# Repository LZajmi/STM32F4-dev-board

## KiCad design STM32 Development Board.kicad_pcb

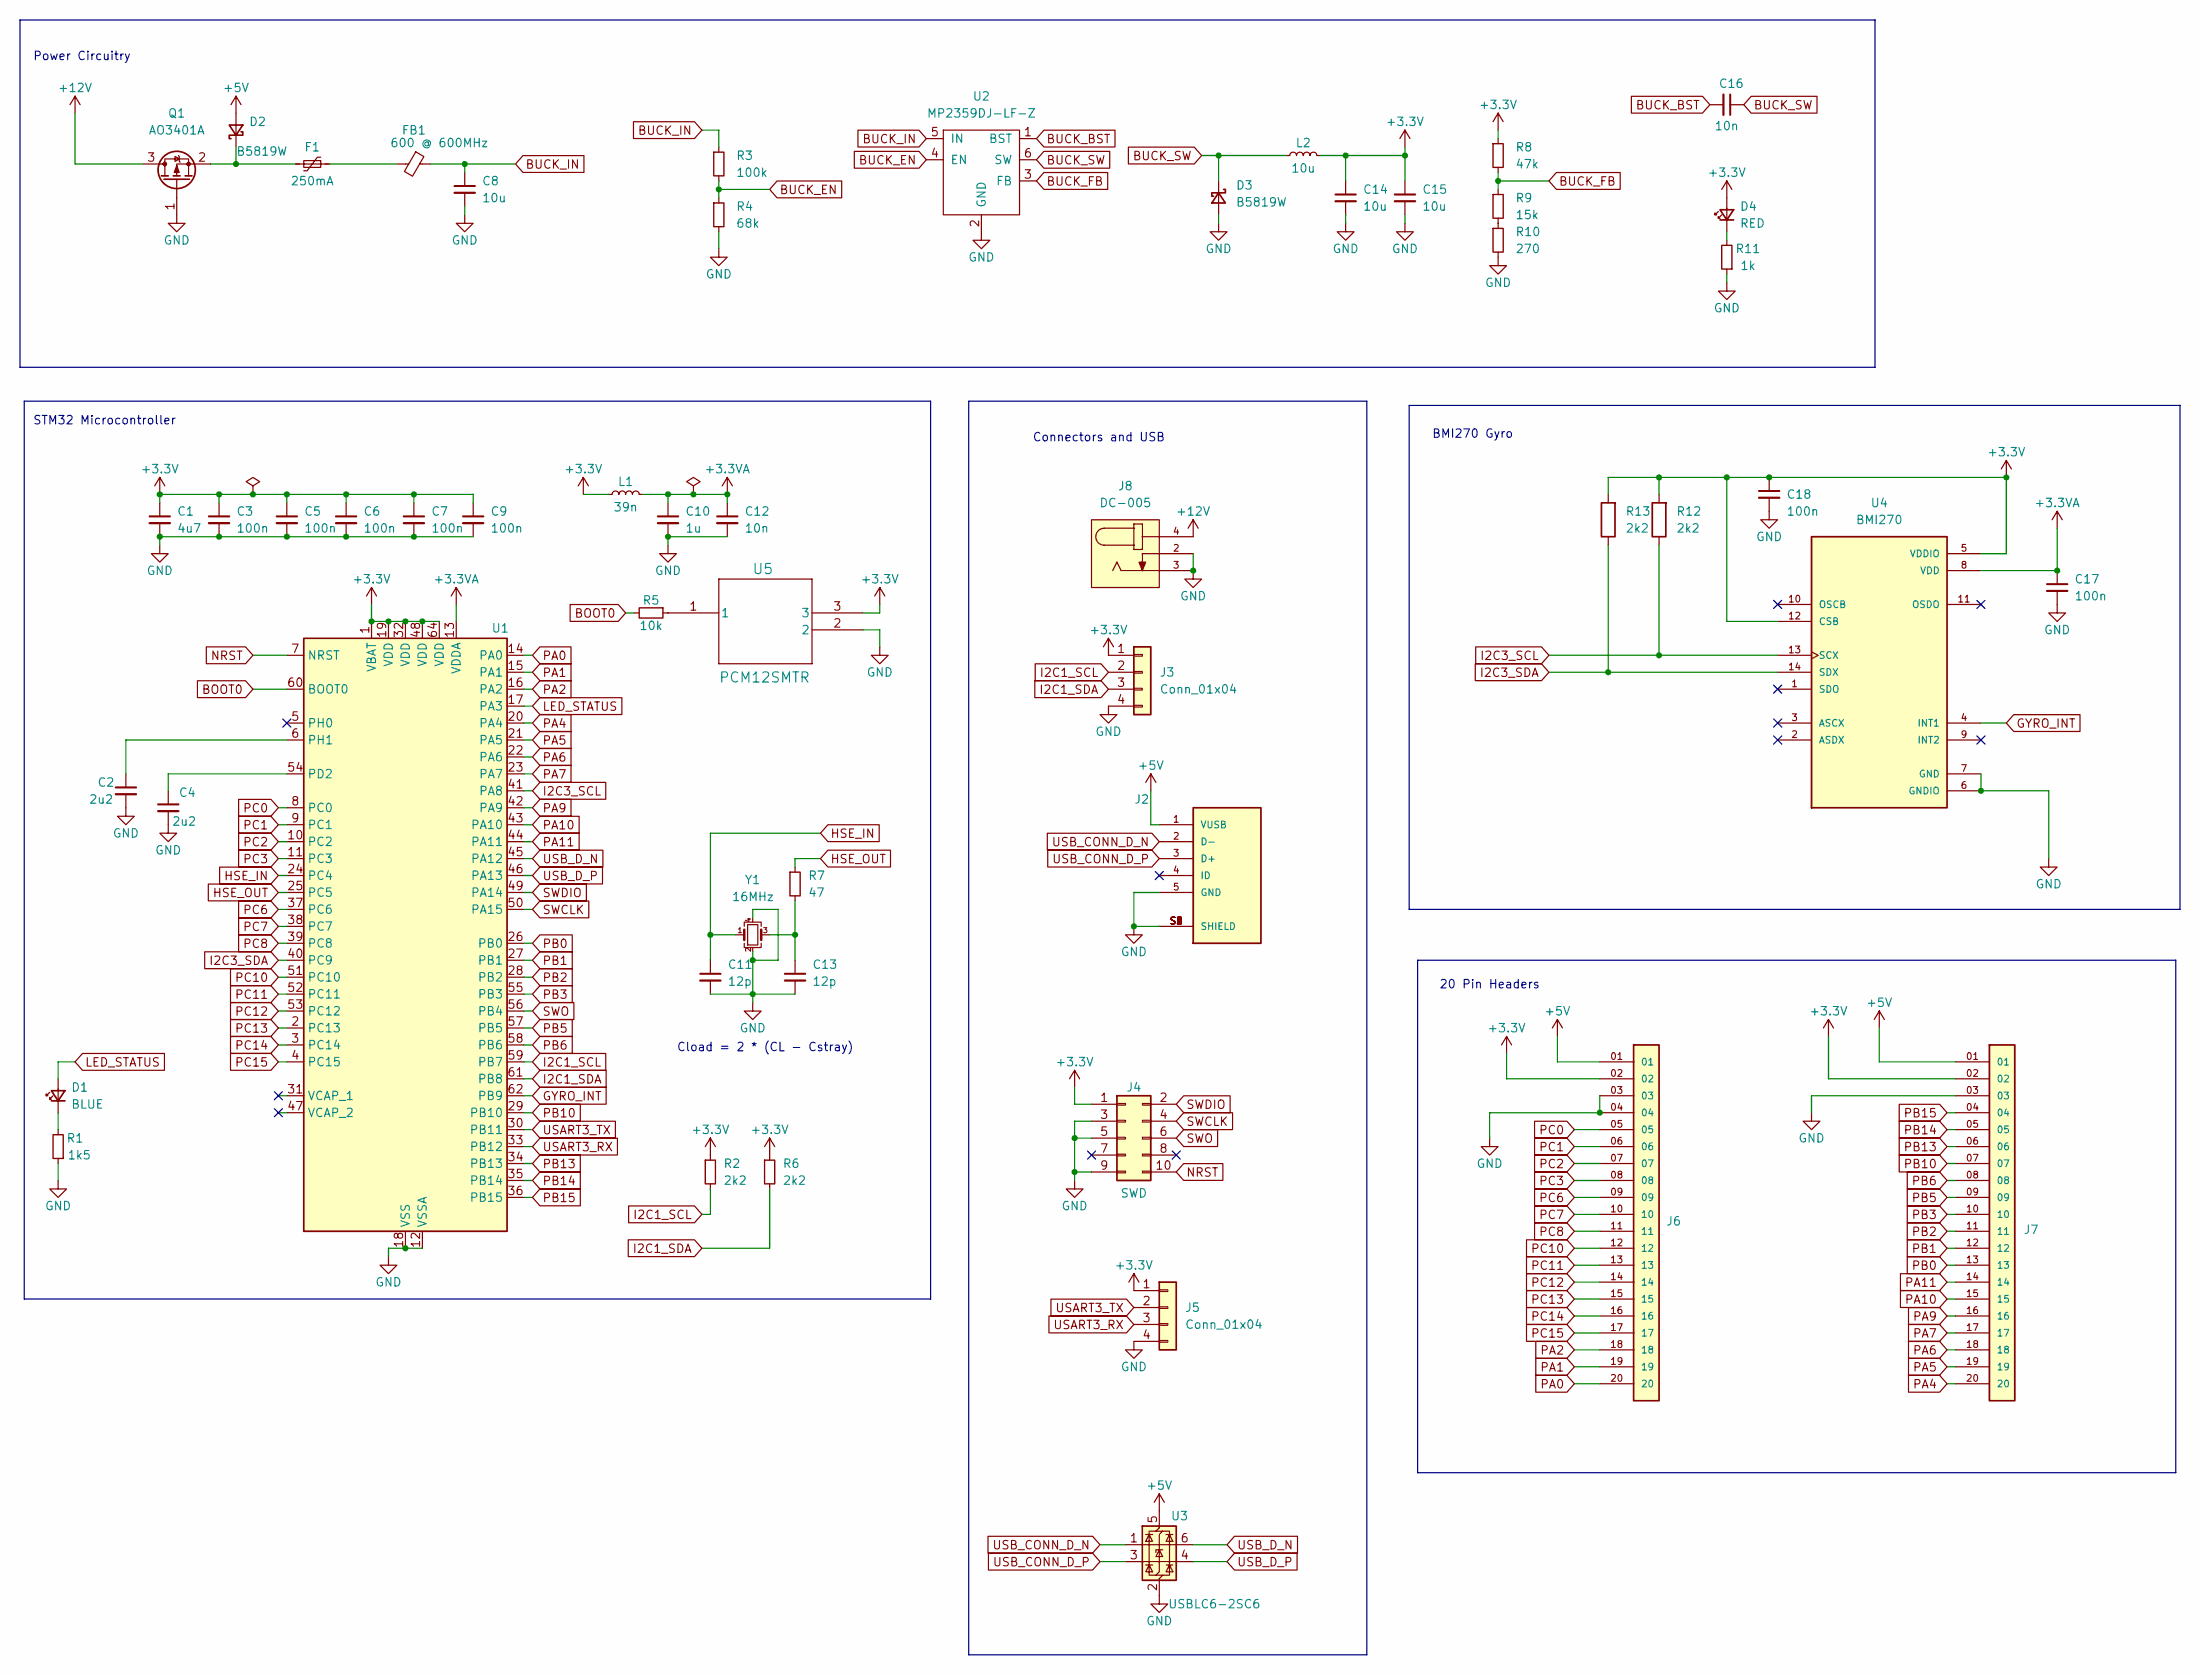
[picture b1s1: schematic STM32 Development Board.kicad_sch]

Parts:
C1: 4u7; C_0603_1608Metric; LCSC Part # C19666
C2, C4: 2u2; C_0603_1608Metric; LCSC Part # C23630
C3, C5, C6, C7, C9, C17, C18: 100n; C_0402_1005Metric; LCSC Part # C1525
C8, C14, C15: 10u; C_1206_3216Metric; LCSC Part # C13585
C10: 1u; C_0402_1005Metric; LCSC Part # C52923
C11, C13: 12p; C_0402_1005Metric; LCSC Part # C1547
C12: 10n; C_0402_1005Metric; LCSC Part # C15195
C16: 10n; C_0603_1608Metric; LCSC Part # C57112
D1: BLUE; LED_0603_1608Metric; LCSC Part # C72041
D2, D3: B5819W; D_SOD-123; LCSC Part # C8598
D4: RED; LED_0603_1608Metric; LCSC Part # C2286
F1: 250mA; Fuse_1206_3216Metric; LCSC Part # C369159
FB1: 600 @ 600MHz; L_0805_2012Metric; LCSC Part # C1017
J2: 10118193-0001LF; AMPHENOL_10118193-0001LF; PARTREV E
J3, J5: Conn_01x04; Molex_PicoBlade_53048-0410_1x04_P1.25mm_Horizontal
J4: SWD; PinHeader_2x05_P1.27mm_Vertical_SMD
J6, J7: TSW-120-24-T-S; SAMTEC_TSW-120-24-T-S; PARTREV R
J8: DC-005; NINIGI_DC-005
L1: 39n; L_0402_1005Metric; LCSC Part # C26443
L2: 10u; IND_SPM6530T-100M-HZ; LCSC Part # C360728
Q1: AO3401A; SOT-23; LCSC Part # C15127
R1: 1k5; R_0603_1608Metric; LCSC Part # C22843
R2, R6: 2k2; R_0402_1005Metric; LCSC Part # C25879
R3: 100k; R_0603_1608Metric; LCSC Part # C25803
R4: 68k; R_0603_1608Metric; LCSC Part # C23231
R5: 10k; R_0402_1005Metric; LCSC Part # C25744
R7: 47; R_0402_1005Metric; LCSC Part # C25118
R8: 47k; R_0603_1608Metric; LCSC Part # C25819
R9: 15k; R_0603_1608Metric; LCSC Part # C22809
R10: 270; R_0603_1608Metric; LCSC Part # C22966
R11: 1k; R_0603_1608Metric; LCSC Part # C21190
R12, R13: 2k2; R_0402_1005Metric
U1: STM32F405RGT6; LQFP-64_10x10mm_P0.5mm; LCSC Part # C15742
U2: MP2359DJ-LF-Z; SOT-23-6; LCSC Part # C14259
U3: USBLC6-2SC6; SOT-23-6; LCSC Part # C7519
U4: BMI270; XDCR_BMI270
U5: PCM12SMTR
Y1: 16MHz; Crystal_SMD_3225-4Pin_3.2x2.5mm; LCSC Part # C13738

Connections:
+3.3VA: C10.1, C12.1, C17.1, L1.2, U1.13 (VDDA), U4.8 (VDD)
+12V: J8.4, Q1.3 (D)
BOOT0: R5.2, U1.60 (BOOT0)
BUCK_BST: C16.2, U2.1 (BST)
BUCK_EN: R3.2, R4.1, U2.4 (EN)
BUCK_FB: R8.2, R9.1, U2.3 (FB)
BUCK_IN: C8.1, FB1.1, R3.1, U2.5 (IN)
BUCK_SW: C16.1, D3.1 (K), L2.1, U2.6 (SW)
GND: C1.2, C2.2, C3.2, C4.2, C5.2, C6.2, C7.2, C8.2, C9.2, C10.2, C11.2, C12.2, C13.2, C14.2, C15.2, C17.2, C18.2, D3.2 (A), J2.5 (GND), J2.S1 (SHIELD), J2.S2 (SHIELD), J2.S3 (SHIELD), J2.S4 (SHIELD), J2.S5 (SHIELD), J2.S6 (SHIELD), J3.4, J4.3, J4.5, J4.9, J5.4, J6.03, J6.04, J7.03, J8.2, J8.3, Q1.1 (G), R1.1, R4.2, R10.2, R11.1, U1.12 (VSSA), U1.18 (VSS), U1.63 (VSS), U2.2 (GND), U3.2 (GND), U4.6 (GNDIO), U4.7 (GND), U5.2, Y1.2, Y1.4; also elsewhere on the board
GYRO_INT: U1.62 (PB9), U4.4 (INT1)
HSE_IN: C11.1, U1.24 (PC4), Y1.1
HSE_OUT: R7.1, U1.25 (PC5)
I2C1_SCL: J3.2, R2.2, U1.59 (PB7)
I2C1_SDA: J3.3, R6.2, U1.61 (PB8)
I2C3_SCL: R12.1, U1.41 (PA8), U4.13 (SCX)
I2C3_SDA: R13.1, U1.40 (PC9), U4.14 (SDX)
LED_STATUS: D1.2 (A), U1.17 (PA3)
NRST: J4.10, U1.7 (NRST)
unnamed: C13.1, R7.2, Y1.3
unnamed: D1.1 (K), R1.2
unnamed: D2.1 (K), F1.2, Q1.2 (S)
unnamed: D4.1 (K), R11.2
unnamed: F1.1, FB1.2
unnamed: R9.2, R10.1
unnamed 24: R5.1, U5.1; also elsewhere on the board
unnamed: C4.1, U1.54 (PD2)
unnamed: C2.1, U1.6 (PH1)
PA0: J6.20, U1.14 (PA0)
PA1: J6.19, U1.15 (PA1)
PA2: J6.18, U1.16 (PA2)
PA4: J7.20, U1.20 (PA4)
PA5: J7.19, U1.21 (PA5)
PA6: J7.18, U1.22 (PA6)
PA7: J7.17, U1.23 (PA7)
PA9: J7.16, U1.42 (PA9)
PA10: J7.15, U1.43 (PA10)
PA11: J7.14, U1.44 (PA11)
PB0: J7.13, U1.26 (PB0)
PB1: J7.12, U1.27 (PB1)
PB2: J7.11, U1.28 (PB2)
PB3: J7.10, U1.55 (PB3)
PB5: J7.09, U1.57 (PB5)
PB6: J7.08, U1.58 (PB6)
PB10: J7.07, U1.29 (PB10)
PB13: J7.06, U1.34 (PB13)
PB14: J7.05, U1.35 (PB14)
PB15: J7.04, U1.36 (PB15)
PC0: J6.05, U1.8 (PC0)
PC1: J6.06, U1.9 (PC1)
PC2: J6.07, U1.10 (PC2)
PC3: J6.08, U1.11 (PC3)
PC6: J6.09, U1.37 (PC6)
PC7: J6.10, U1.38 (PC7)
PC8: J6.11, U1.39 (PC8)
PC10: J6.12, U1.51 (PC10)
PC11: J6.13, U1.52 (PC11)
PC12: J6.14, U1.53 (PC12)
PC13: J6.15, U1.2 (PC13)
PC14: J6.16, U1.3 (PC14)
PC15: J6.17, U1.4 (PC15)
SWCLK: J4.4, U1.50 (PA15)
SWDIO: J4.2, U1.49 (PA14)
SWO: J4.6, U1.56 (PB4)
USART3_RX: J5.3, U1.33 (PB12)
USART3_TX: J5.2, U1.30 (PB11)
USB_CONN_D_N: J2.2 (D-), U3.1 (I/O1)
USB_CONN_D_P: J2.3 (D+), U3.3 (I/O2)
USB_D_N: U1.45 (PA12), U3.6 (I/O1)
USB_D_P: U1.46 (PA13), U3.4 (I/O2)

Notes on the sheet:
Cload = 2 * (CL - Cstray)
20 Pin Headers
BMI270 Gyro
STM32 Microcontroller
Connectors and USB
Power Circuitry

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
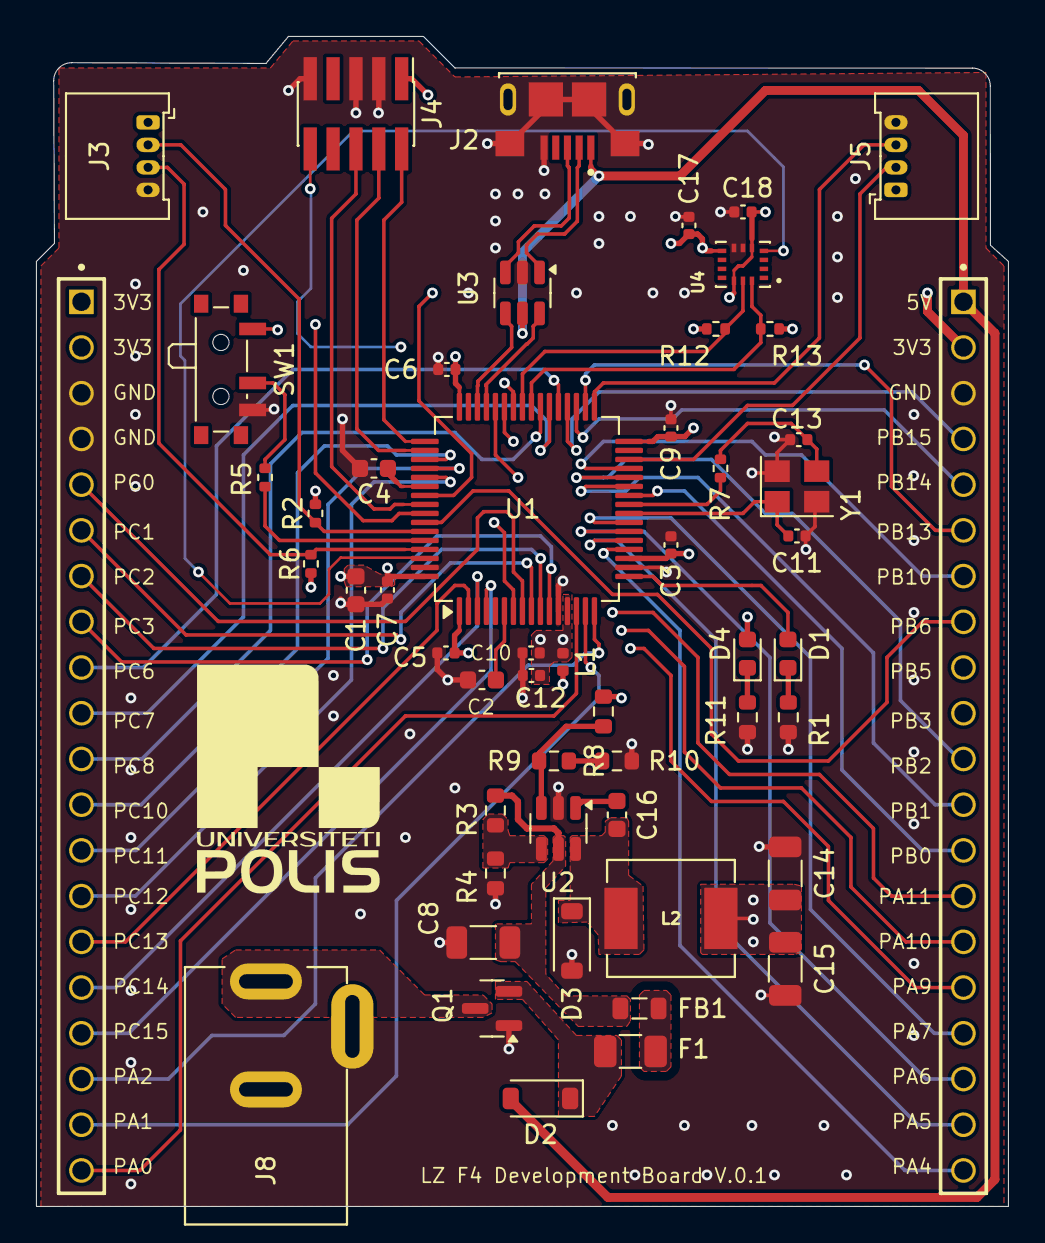
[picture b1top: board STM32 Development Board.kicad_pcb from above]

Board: 4 copper layers, 54.0 x 65.0 mm, 53 parts (0 on the bottom side), 71 nets.

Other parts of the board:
SW1: SW_SPDT; SW_SPDT_PCM12

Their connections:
GND: SW1.3 (C); also elsewhere on the board
unnamed 24: SW1.2 (B); also elsewhere on the board

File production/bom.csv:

Designator,Footprint,Quantity,Value,LCSC Part #
C1,603,1,4u7,C19666
C10,402,1,1u,C52923
"C11, C13",402,2,12p,C1547
C12,402,1,10n,C15195
"C14, C15, C8",1206,3,10u,C13585
C16,603,1,10n,C57112
"C17, C18, C3, C5, C6, C7, C9",402,7,100n,C1525
"C2, C4",603,2,2u2,C23630
D1,603,1,BLUE,C72041
"D2, D3",D_SOD-123,2,B5819W,C8598
D4,603,1,RED,C2286
F1,1206,1,250mA,C369159
FB1,805,1,600 @ 600MHz,C1017
J2,AMPHENOL_10118193-0001LF,1,10118193-0001LF,C132562
"J3, J5",Molex_PicoBlade_53048-0410_1x04_P1.25mm_Horizontal,2,Conn_01x04,C588275
J4,PinHeader_2x05_P1.27mm_Vertical_SMD,1,SWD,
"J6, J7",SAMTEC_TSW-120-24-T-S,2,TSW-120-24-T-S,
J8,NINIGI_DC-005,1,DC-005,C7471792
L1,402,1,39n,C26443
L2,IND_SPM6530T-100M-HZ,1,10u,C360728
Q1,SOT-23,1,AO3401A,C15127
R1,603,1,1k5,C22843
R10,603,1,270,C22966
R11,603,1,1k,C21190
"R12, R13",402,2,2k2,C25879
"R2, R6",402,2,2k2,C25879
R3,603,1,100k,C25803
R4,603,1,68k,C23231
R5,402,1,10k,C25744
R7,402,1,47,C25118
R8,603,1,47k,C25819
R9,603,1,15k,C22809
SW1,SW_SPDT_PCM12,1,SW_SPDT,C221841
U1,LQFP-64_10x10mm_P0.5mm,1,STM32F405RGT6,C15742
U2,SOT-23-6,1,MP2359DJ-LF-Z,C14259
U3,SOT-23-6,1,USBLC6-2SC6,C7519
U4,XDCR_BMI270,1,BMI270,C2836813
Y1,Crystal_SMD_3225-4Pin_3.2x2.5mm,1,16MHz,C13738

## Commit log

2025-01-15 Upload
2025-03-24 Library Upload
